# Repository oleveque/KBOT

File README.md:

# KBOT

Un KBOT est un petit "robot sandwich" doté de deux roues motrices (moteurs+codeurs), d'une Arduino Méga 2560, d'un écran LCD 16x2, d'une batterie 3S… C'est une fabrication maison que réalise les premières années du club de robotique de l'ENS Paris-Saclay pour acquérir les bases de la robotique & se familiariser avec la programmation à travers l'IDE Arduino.
Pour plus d'information consultez notre site [[Kro]bot](https://wiki.crans.org/ClubKrobot).

## Informations générales :
* *Mode de déplacement du robot :* entraînement différenciel
* *Moyens de communication :* USB, Bluetooth
* *Version actuelle :* 2.0 (Révisé par Y. Labbe & O. Lévêque - Sept. 2017)

## Ports I/O :
* 1 module Bluetooth (HC-06) ;
* 1 port SHARP (GP2D12) ;
* 1 port Servo (SG90) ;
* 1 port pour controler le niveau de charge de la batterie ;
* 1 Buzzer ;
* 1 port extension pour 5 Boutons ;
* 1 port extension pour 10 Leds.

## Amélioration pour la version 2.1 :
* CAO -> simplifier les entretoises des roues + ajuster l'empreinte de l'écran LCD + ajouter un système de fixations pour les cales avant/arrière
* PCB -> corriger l'agencement buzzer/bluetooth + corriger les couleurs des fils des encoders + changer le sens de la nappe PowerDistributor-PropulsionShield + changer le sens de connecteur batterie + amener la led 13 sur le UI
* Arduino -> Ajouter 1 exemple d'Asserv

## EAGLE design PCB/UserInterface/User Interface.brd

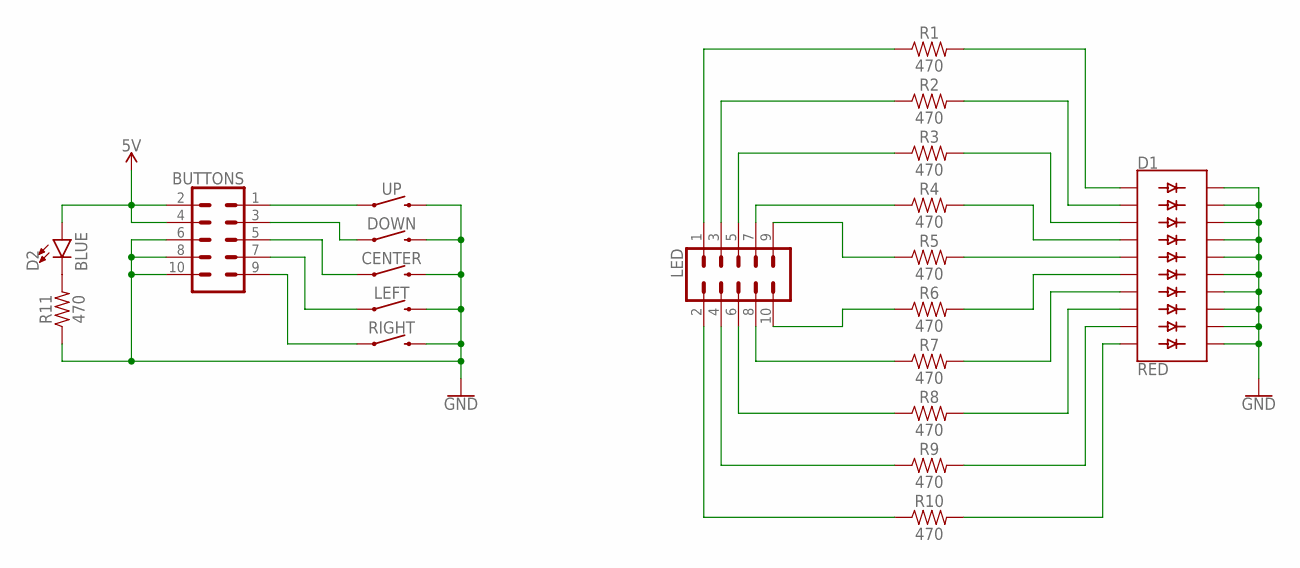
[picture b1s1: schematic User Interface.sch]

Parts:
BUTTONS: CONN_05X2SHD; 2X5-SHROUDED
CENTER: MOMENTARY-SWITCH-SPST-PTH-6.0MM; TACTILE_SWITCH_PTH_6.0MM
D1: RED; LED_BARGRAPH_10
D2: BLUE; LED-1206
DOWN: MOMENTARY-SWITCH-SPST-PTH-6.0MM; TACTILE_SWITCH_PTH_6.0MM
LED: CONN_05X2SHD; 2X5-SHROUDED
LEFT: MOMENTARY-SWITCH-SPST-PTH-6.0MM; TACTILE_SWITCH_PTH_6.0MM
R1, R2, R3, R4, R5, R6, R7, R8, R9, R10, R11: 470; 1206
RIGHT: MOMENTARY-SWITCH-SPST-PTH-6.0MM; TACTILE_SWITCH_PTH_6.0MM
UP: MOMENTARY-SWITCH-SPST-PTH-6.0MM; TACTILE_SWITCH_PTH_6.0MM

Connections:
5V: BUTTONS.2, BUTTONS.4, D2.A
GND: BUTTONS.6, BUTTONS.8, BUTTONS.10, CENTER.3 (2), D1.11 (C9), D1.12 (C8), D1.13 (C7), D1.14 (C6), D1.15 (C5), D1.16 (C4), D1.17 (C3), D1.18 (C2), D1.19 (C1), D1.20 (C), DOWN.3 (2), LEFT.3 (2), R11.1, RIGHT.3 (2), UP.3 (2)
unnamed: D1.1 (A), R1.2
unnamed: D1.2 (A1), R2.2
unnamed: D1.3 (A2), R3.2
unnamed: D1.4 (A3), R4.2
unnamed: D1.5 (A4), R5.2
unnamed: D1.6 (A5), R6.2
unnamed: D1.7 (A6), R7.2
unnamed: D1.8 (A7), R8.2
unnamed: D1.9 (A8), R9.2
unnamed: D1.10 (A9), R10.2
unnamed: LED.9, R5.1
unnamed: LED.7, R4.1
unnamed: LED.5, R3.1
unnamed: LED.3, R2.1
unnamed: LED.1, R1.1
unnamed: LED.10, R6.1
unnamed: LED.8, R7.1
unnamed: LED.6, R8.1
unnamed: LED.4, R9.1
unnamed: LED.2, R10.1
unnamed: BUTTONS.1, UP.1
unnamed: BUTTONS.3, DOWN.1
unnamed: BUTTONS.5, CENTER.1
unnamed: BUTTONS.7, LEFT.1
unnamed: BUTTONS.9, RIGHT.1
unnamed: D2.C, R11.2

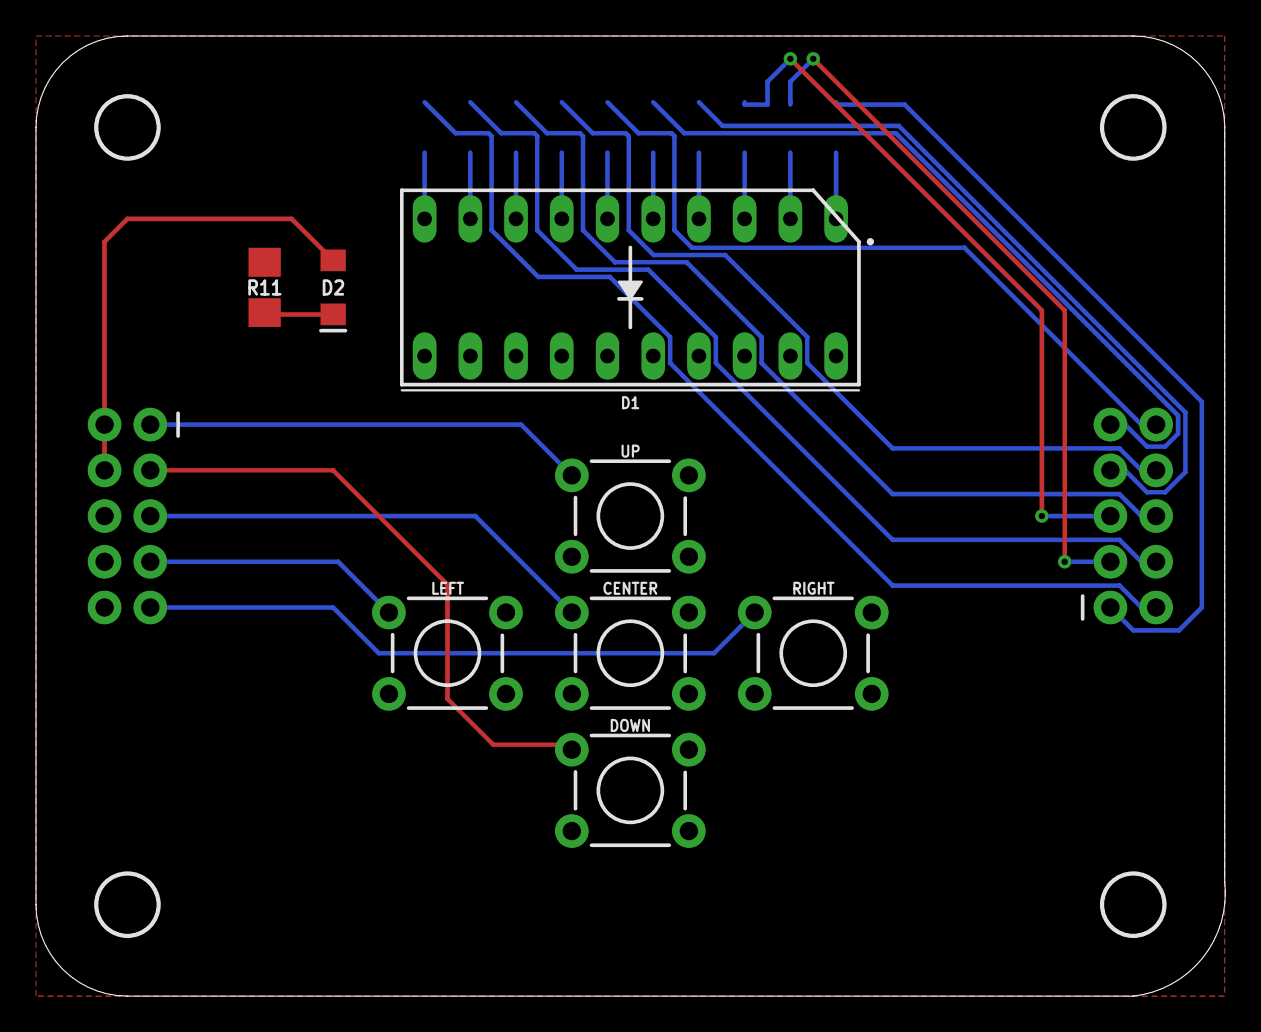
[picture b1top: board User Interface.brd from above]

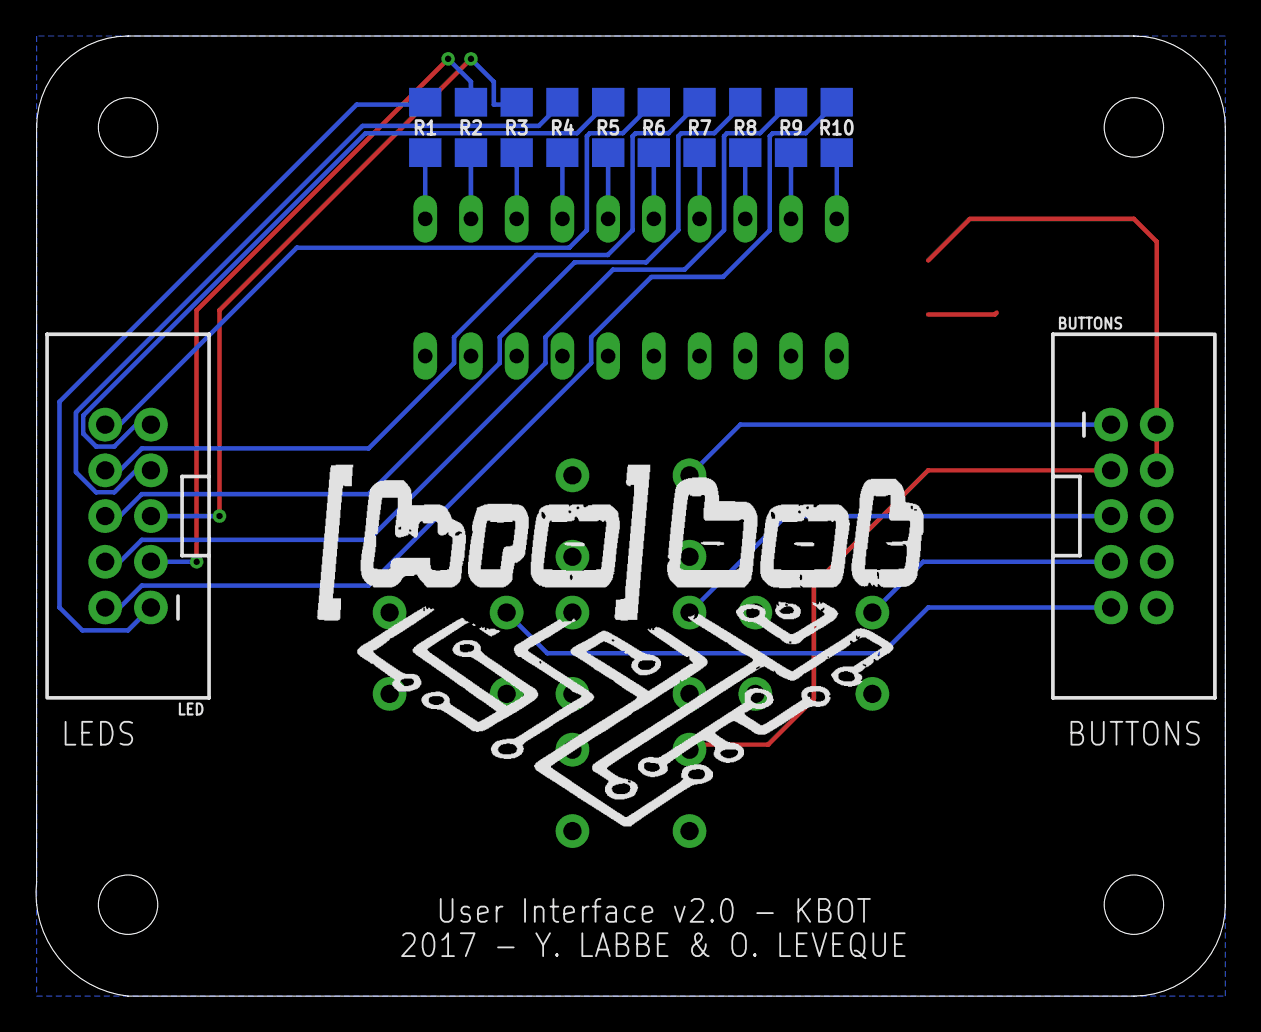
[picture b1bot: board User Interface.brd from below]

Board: 2 copper layers, 66.1 x 53.3 mm, 25 parts (13 on the bottom side), 28 nets.

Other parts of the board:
U$1, U$2, U$3, U$4: 3,3
U$5: LOGO_33MM

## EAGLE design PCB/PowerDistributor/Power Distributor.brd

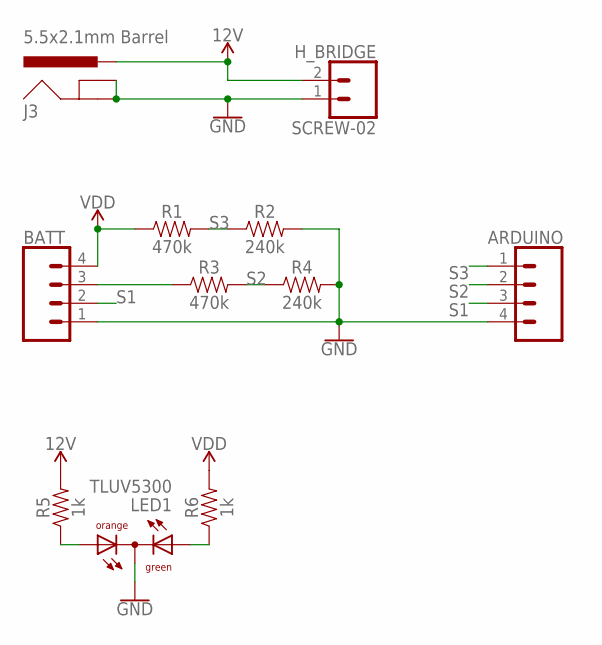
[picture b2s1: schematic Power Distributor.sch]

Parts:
ARDUINO: JST-XH-04-PIN-LONG-PAD; JST-XH-04-PACKAGE-LONG-PAD
BATT: JST-XH-04-PIN-LONG-PAD; JST-XH-04-PACKAGE-LONG-PAD
H_BRIDGE: SCREW-02
J3: 5.5x2.1mm Barrel; POWER_JACK_SMD
LED1: TLUV5300
R1, R3: 470k; 1206
R2, R4: 240k; 1206
R5, R6: 1k; 1206

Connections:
12V: H_BRIDGE.2, J3.VIN0 (PWR), R5.2
GND: ARDUINO.4, BATT.1, H_BRIDGE.1, J3.GND (GNDBREAK), J3.P$4 (GND), LED1.CC, R2.2, R4.2
unnamed: BATT.3, R3.1
unnamed: LED1.AO, R5.1
unnamed: LED1.AG, R6.1
S1: ARDUINO.3, BATT.2
S2: ARDUINO.2, R3.2, R4.1
S3: ARDUINO.1, R1.2, R2.1
VDD: BATT.4, R1.1, R6.2

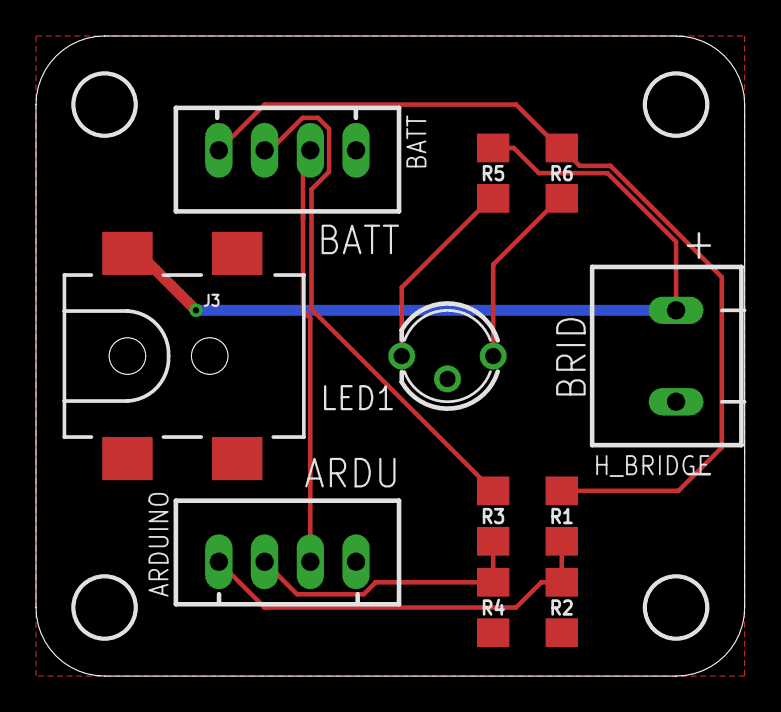
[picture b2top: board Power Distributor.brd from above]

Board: 2 copper layers, 39.4 x 35.6 mm, 16 parts (1 on the bottom side), 9 nets.

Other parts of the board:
U$1, U$2, U$3, U$4: 3,3
U$5: LOGO_22MM

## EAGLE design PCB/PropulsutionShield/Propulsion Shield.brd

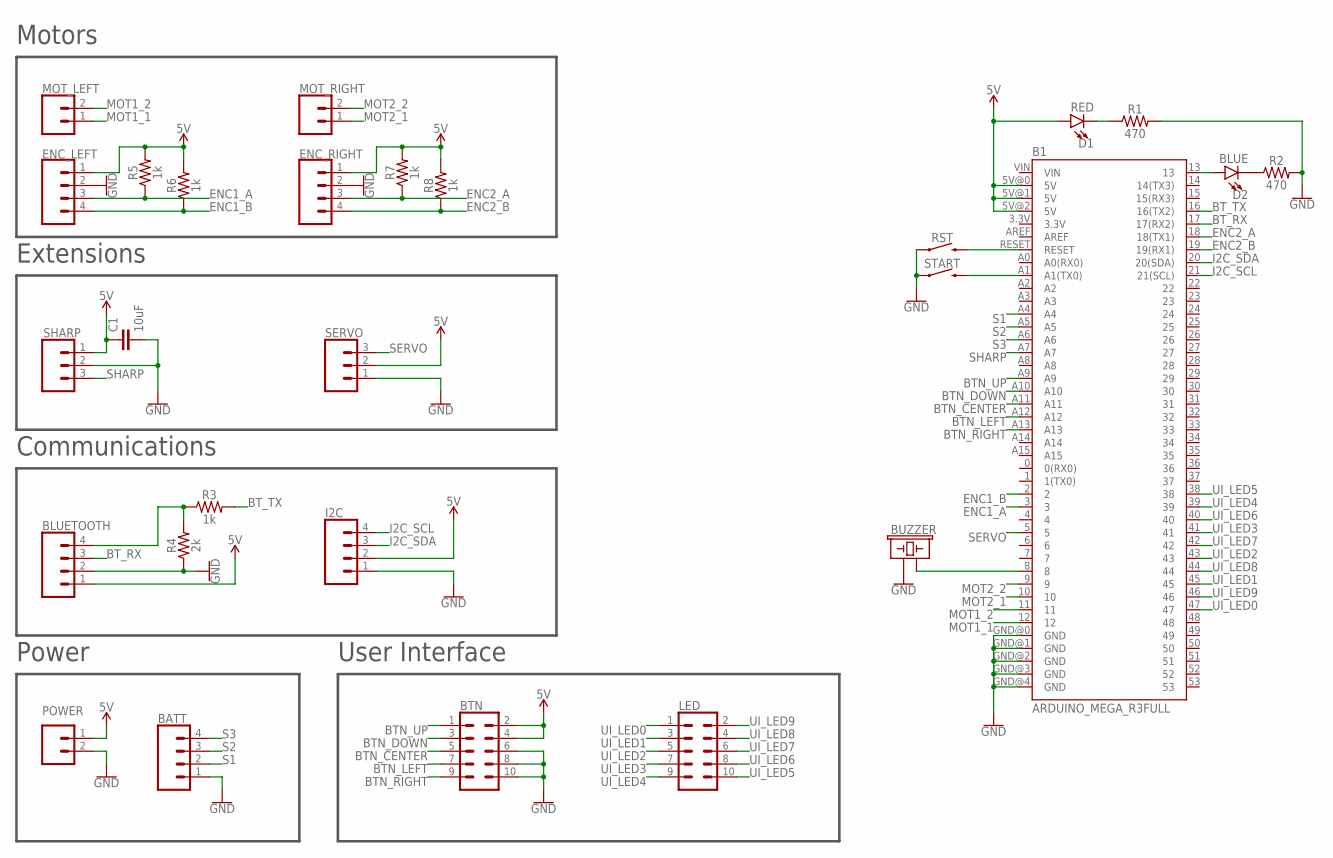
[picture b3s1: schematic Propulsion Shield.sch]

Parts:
B1: ARDUINO_MEGA_R3FULL; ARDUINO_MEGA
BATT: JST-XH-04-PIN-LONG-PAD; JST-XH-04-PACKAGE-LONG-PAD
BLUETOOTH: CONN_04; 1X04
BTN: CONN_05X2SHD; 2X5-SHROUDED
BUZZER: BUZZER-PTH; BUZZER-12MM
C1: 10uF; 1206
D1: RED; LED-1206
D2: BLUE; LED-1206
ENC_LEFT: JST-XH-04-PIN-LONG-PAD; JST-XH-04-PACKAGE-LONG-PAD
ENC_RIGHT: JST-XH-04-PIN-LONG-PAD; JST-XH-04-PACKAGE-LONG-PAD
I2C: CONN_04; 1X04
LED: CONN_05X2SHD; 2X5-SHROUDED
MOT_LEFT: CONN_02; 1X02
MOT_RIGHT: CONN_02; 1X02
POWER: JST-XH-02-PIN-LONG-PAD; JST-XH-02-PACKAGE-LONG-PAD
R1, R2: 470; 1206
R3, R5, R6, R7, R8: 1k; 1206
R4: 2k; 1206
RST: MOMENTARY-SWITCH-SPST-PTH-6.0MM; TACTILE_SWITCH_PTH_6.0MM
SERVO: CONN_03; 1X03
SHARP: JST-PH3
START: MOMENTARY-SWITCH-SPST-PTH-6.0MM; TACTILE_SWITCH_PTH_6.0MM

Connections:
5V: B1.5V@0 (5V), B1.5V@1 (5V), B1.5V@2 (5V), BLUETOOTH.1, BTN.2, BTN.4, C1.1, D1.A, ENC_LEFT.1, ENC_RIGHT.1, I2C.2, POWER.1, R5.2, R6.2, R7.2, R8.2, SERVO.2, SHARP.1
BTN_CENTER: B1.A11, BTN.5
BTN_DOWN: B1.A10, BTN.3
BTN_LEFT: B1.A12, BTN.7
BTN_RIGHT: B1.A13, BTN.9
BTN_UP: B1.A9, BTN.1
BT_RX: B1.17 (17(RX2)), BLUETOOTH.3
BT_TX: B1.16 (16(TX2)), R3.2
BUZZER: B1.8, BUZZER.- (2)
ENC1_A: B1.3, ENC_LEFT.3, R5.1
ENC1_B: B1.2, ENC_LEFT.4, R6.1
ENC2_A: B1.18 (18(TX1)), ENC_RIGHT.3, R7.1
ENC2_B: B1.19 (19(RX1)), ENC_RIGHT.4, R8.1
GND: B1.GND@0 (GND), B1.GND@1 (GND), B1.GND@2 (GND), B1.GND@3 (GND), B1.GND@4 (GND), BATT.1, BLUETOOTH.2, BTN.6, BTN.8, BTN.10, BUZZER.+ (1), C1.2, ENC_LEFT.2, ENC_RIGHT.2, I2C.1, POWER.2, R1.2, R2.2, R4.1, RST.1, SERVO.1, SHARP.2, START.1
I2C_SCL: B1.21 (21(SCL)), I2C.4
I2C_SDA: B1.20 (20(SDA)), I2C.3
MOT1_1: B1.12, MOT_LEFT.1
MOT1_2: B1.11, MOT_LEFT.2
MOT2_1: B1.10, MOT_RIGHT.1
MOT2_2: B1.9, MOT_RIGHT.2
unnamed: B1.RESET, RST.3 (2)
unnamed: D1.C, R1.1
unnamed: B1.13, D2.A
unnamed: D2.C, R2.1
unnamed: BLUETOOTH.4, R3.1, R4.2
unnamed: B1.A1 (A1(TX0)), START.3 (2)
S1: B1.A4, BATT.2
S2: B1.A5, BATT.3
S3: B1.A6, BATT.4
SERVO: B1.5, SERVO.3
SHARP: B1.A7, SHARP.3
UI_LED0: B1.47, LED.1
UI_LED1: B1.45, LED.3
UI_LED2: B1.43, LED.5
UI_LED3: B1.41, LED.7
UI_LED4: B1.39, LED.9
UI_LED5: B1.38, LED.10
UI_LED6: B1.40, LED.8
UI_LED7: B1.42, LED.6
UI_LED8: B1.44, LED.4
UI_LED9: B1.46, LED.2

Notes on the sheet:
Motors
Extensions
Communications
Power
User Interface

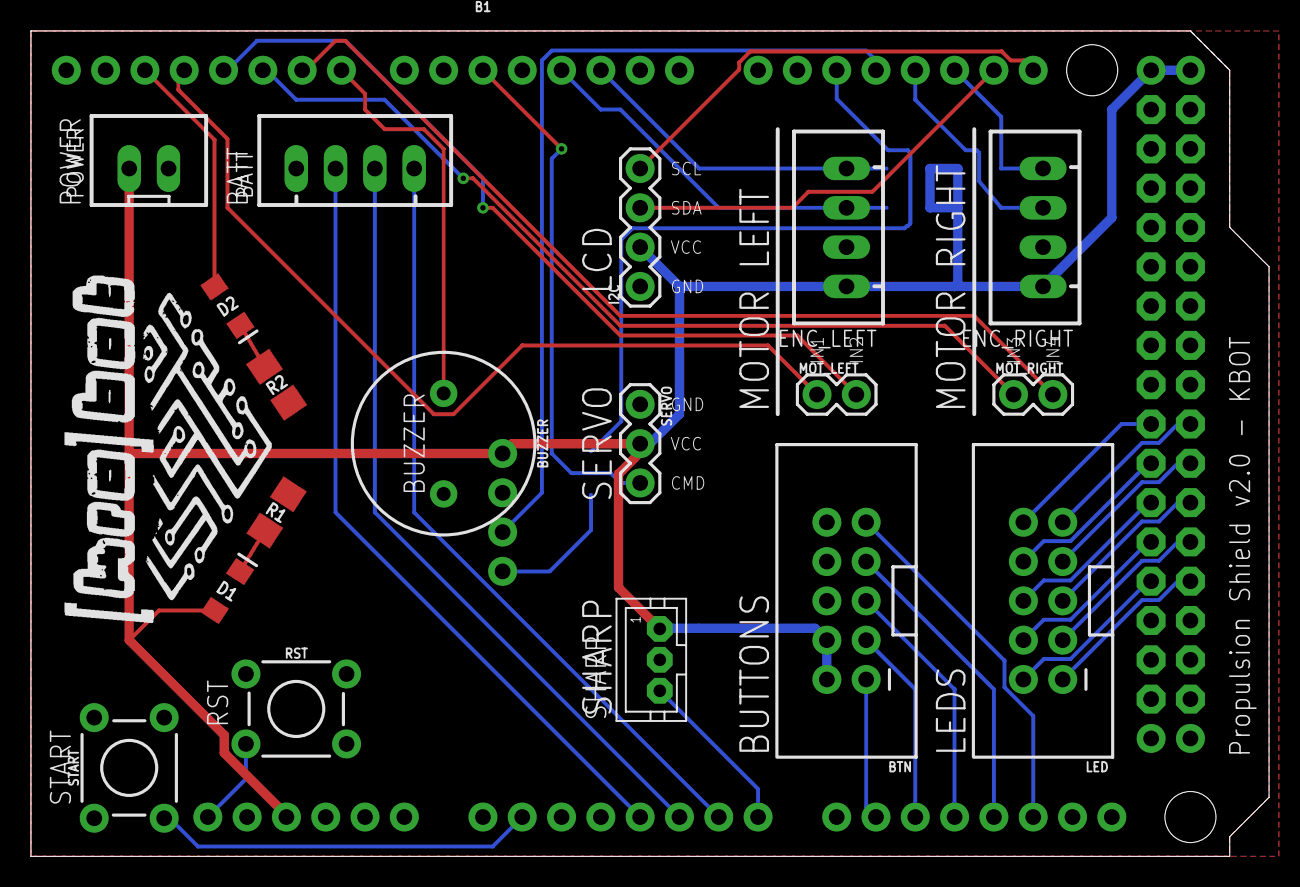
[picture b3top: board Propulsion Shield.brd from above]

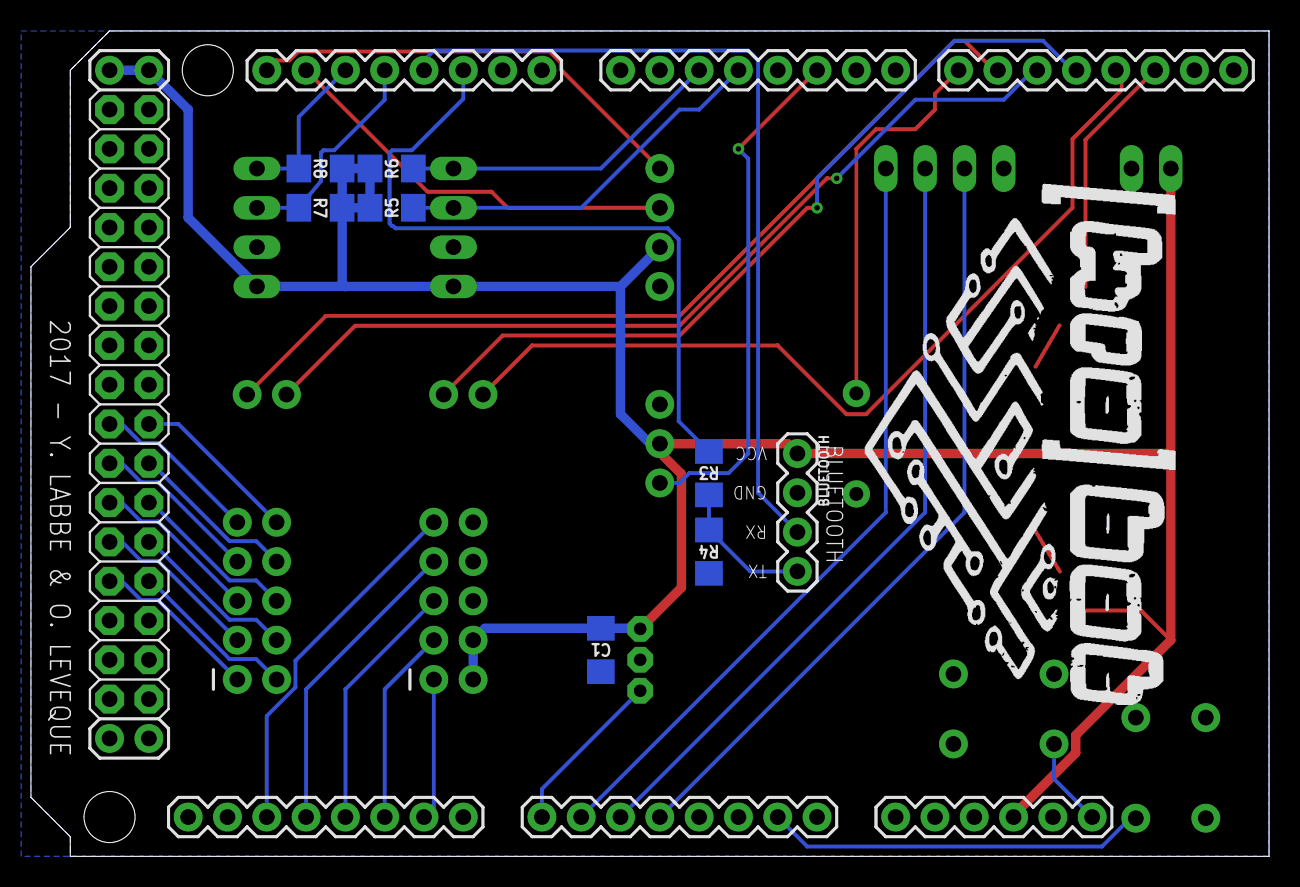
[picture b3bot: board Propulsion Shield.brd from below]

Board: 2 copper layers, 80.0 x 53.3 mm, 29 parts (9 on the bottom side), 41 nets.

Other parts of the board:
U$1: LOGO_22MM
U$2: LOGO_33MM

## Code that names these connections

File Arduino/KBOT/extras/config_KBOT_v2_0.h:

/************************************************************************
 * File : config_KBOT_v2_0.h                                         	*
 *  >> BRAINZY Library <<                                               *
 *  Project repo  : http://github.com/oleveque/BRAINZY                  *
 *  Documentation : http://docs.mr-robotics.com/                        *
 *																		*
 *  This file define the KBOT v2.0 pin names 							*
 *																		*
 * Copyright : (c) 2017, Olivier Lévêque <oleveque@crans.org>     	    *
 ************************************************************************/

#ifndef __BRAINZY_CONFIG_H
#define __BRAINZY_CONFIG_H

/* ------------------- 
  For BRAINZY Lib
------------------- */

//Motor LEFT
#define MOT1_1 		12
#define MOT1_2 		11
#define ENC1_A 		3
#define ENC1_B 		2

//Motor RIGHT
#define MOT2_1 		10
#define MOT2_2 		9
#define ENC2_A 		18
#define ENC2_B 		19

//Motor FRONT
#define MOT3_1 		255	 //255 if not exists
#define MOT3_2 		255  //255 if not exists
#define ENC3_A 		255  //255 if not exists
#define ENC3_B 		255  //255 if not exists

//Serial
#define USB 		Serial
#define Bluetooth 	Serial2

//I2C
#define I2C_SDA 	20
#define I2C_SCL 	21
#define I2C 		Wire

//Power Monitoring
#define BATT1 		A4
#define BATT2 		A5
#define BATT3 		A6

//Other
#define BUZZER 		8
#define BUILTIN_LED 13

/* ------------------- 
  Other
------------------- */

//LED
#define LED0 		47
#define LED1 		45
#define LED2 		43
#define LED3 		41
#define LED4 		39
#define LED5 		38
#define LED6 		40
#define LED7 		42
#define LED8 		44
#define LED9 		46

//Buttons
#define BTN_UP 		A9
#define BTN_DOWN 	A10
#define BTN_CENTER 	A11
#define BTN_LEFT 	A12
#define BTN_RIGHT 	A13
#define BTN_START 	A1

//Other
#define SHARP 		A7
#define SERVO		5


#endif //__BRAINZY_CONFIG_H

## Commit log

2017-09-19 Create readme file
2017-09-19 add pcb files
2017-09-19 add config file
2017-09-28 add cao files
2017-10-10 add PCB pictures
2017-10-11 add screw-02 connector
2017-10-11 update power distributor
2017-10-11 update user interface
2017-10-11 update propulsion shield
2017-10-11 add updates for KBOT V2.1
2017-10-18 Add Arduino examples
2017-10-22 Auto stash before merge of "master" and "origin/master"
2017-10-22 Update arduino ino
2017-10-22 Update file organizations
2017-10-22 Rename and reorganize CAO files
2017-11-28 Update BUILTIN_LED pin name
2017-11-28 Update properties file
2017-11-28 Add LiquidCrystal_I2C library as module
2017-11-29 Add examples
2017-11-29 Add button example
2017-12-11 Add sourcing components
2017-12-11 Reorganize files
2017-12-11 Add files for BRAINZY Lib
2017-12-21 Update BUZZER example
2017-12-21 Rename sourcing file
2018-01-06 Removed submodule Arduino Libraries/LiquidCrystal_I2C
2018-01-06 Add LiquidCrystal_I2C as a submodule

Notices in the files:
parts and their libraries:
SparkFun-Connectors: Licensing: Creative Commons ShareAlike 4.0 International - https://creativecommons.org/licenses/by-sa/4.0
